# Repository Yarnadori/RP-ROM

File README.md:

# RP-ROM

M27C256 EPROM エミュレータ。RP2354A (RP2350 QFN-60) を搭載した自作 PCB で、32KB の ROM コンテンツを USB 経由で書き込み・読み出しできる。

## 概要

| 項目             | 内容                                            |
| ---------------- | ----------------------------------------------- |
| 対象 EPROM       | M27C256 互換 (32KB, 15-bit address, 8-bit data) |
| MCU              | RP2354A (RP2350 QFN-60, 360 MHz 動作)           |
| インターフェース | USB-C (CDC Serial)                              |
| フラッシュ保持   | 電源断後も ROM データを内蔵フラッシュに保存     |

## リポジトリ構成

```text
RP-ROM/
├── hardware/          # KiCad プロジェクト (回路図・PCB)
│   └── production/    # 製造用ファイル (BOM, Gerber, 部品配置)
├── software/          # RP2350 ファームウェア (C / Pico SDK)
│   └── main.c
└── tools/             # ホスト側 Python ツール
    └── rom_tool.py
```

## ハードウェア

KiCad で設計。製造 BOM の概要:

| Ref                 | 数量 | 部品 / 値                   | パッケージ / 備考              | LCSC Part # |
| ------------------- | ---: | --------------------------- | ------------------------------ | ----------- |
| IC1                 |    1 | RP2354A                     | QFN-60, メイン MCU             | C41378174   |
| U1                  |    1 | RT9080-33GJ5                | TSOT-23-5, 3.3V LDO            | C7528830    |
| J1                  |    1 | USB_C_Receptacle_USB2.0_16P | USB-C                          | C2843970    |
| J2, J3              |    2 | Conn_01x14_Pin              | 1×14 ピンヘッダ                |             |
| J4                  |    1 | Conn_01x03                  | JST SH 3P, デバッガー          | C7430452    |
| SW1                 |    1 | SW_Push                     | TS-1088 系タクトスイッチ       | C720477     |
| Y1                  |    1 | 12 MHz                      | 3225 4-pin 水晶                | C9002       |
| L1                  |    1 | 3.3uH                       | AOTA-B201610S3R3-101-T         | C42411119   |
| D1, D2              |    2 | RB521S-30                   | SOD-523 ショットキーダイオード | C8523       |
| D3                  |    1 | LED                         | 0402                           | C51933305   |
| C1                  |    1 | 4.7nF                       | 0402                           | C1538       |
| C2, C3              |    2 | 1uF                         | 0402                           | C52923      |
| C5, C8              |    2 | 15pF                        | 0402                           | C1548       |
| C9, C10, C11        |    3 | 4.7uF                       | 0402                           | C23733      |
| C4, C6, C7, C12-C14 |    6 | 0.1uF                       | 0402                           | C1525       |
| R1                  |    1 | 1MΩ                         | 0402                           | C26083      |
| R2, R3              |    2 | 5.1kΩ                       | 0402                           | C25905      |
| R4, R5, R6          |    3 | 1k                          | 0402                           | C11702      |
| R7, R8              |    2 | 27Ω                         | 0402                           | C25100      |
| R9                  |    1 | 33Ω                         | 0402                           | C25105      |

製造ファイルは `hardware/production/` に格納。

## ファームウェア

### 必要環境

- [Raspberry Pi Pico SDK](https://github.com/raspberrypi/pico-sdk) v2.2.0

### 動作

- **Core 1**: ROM アドレス線監視・データ出力 (フラッシュ不使用のタイトループ、360 MHz)
- **Core 0**: USB シリアル経由のコマンド処理
- **永続化**: 書き込んだ ROM データを内蔵フラッシュ末尾 36KB に保存。電源投入時に自動ロード。

## ツール (tools/)

Python 製のホストツール。詳細は [tools/README.md](tools/README.md) を参照。

```bash
cd tools
uv run rom_tool.py write COM3 firmware.hex
uv run rom_tool.py read  COM3 dump.bin
uv run rom_tool.py verify COM3 firmware.hex
uv run rom_tool.py erase COM3
uv run rom_tool.py info  COM3
```

対応フォーマット: `.bin` / Intel HEX (`.hex`)

## ライセンス

[MIT License](LICENSE)

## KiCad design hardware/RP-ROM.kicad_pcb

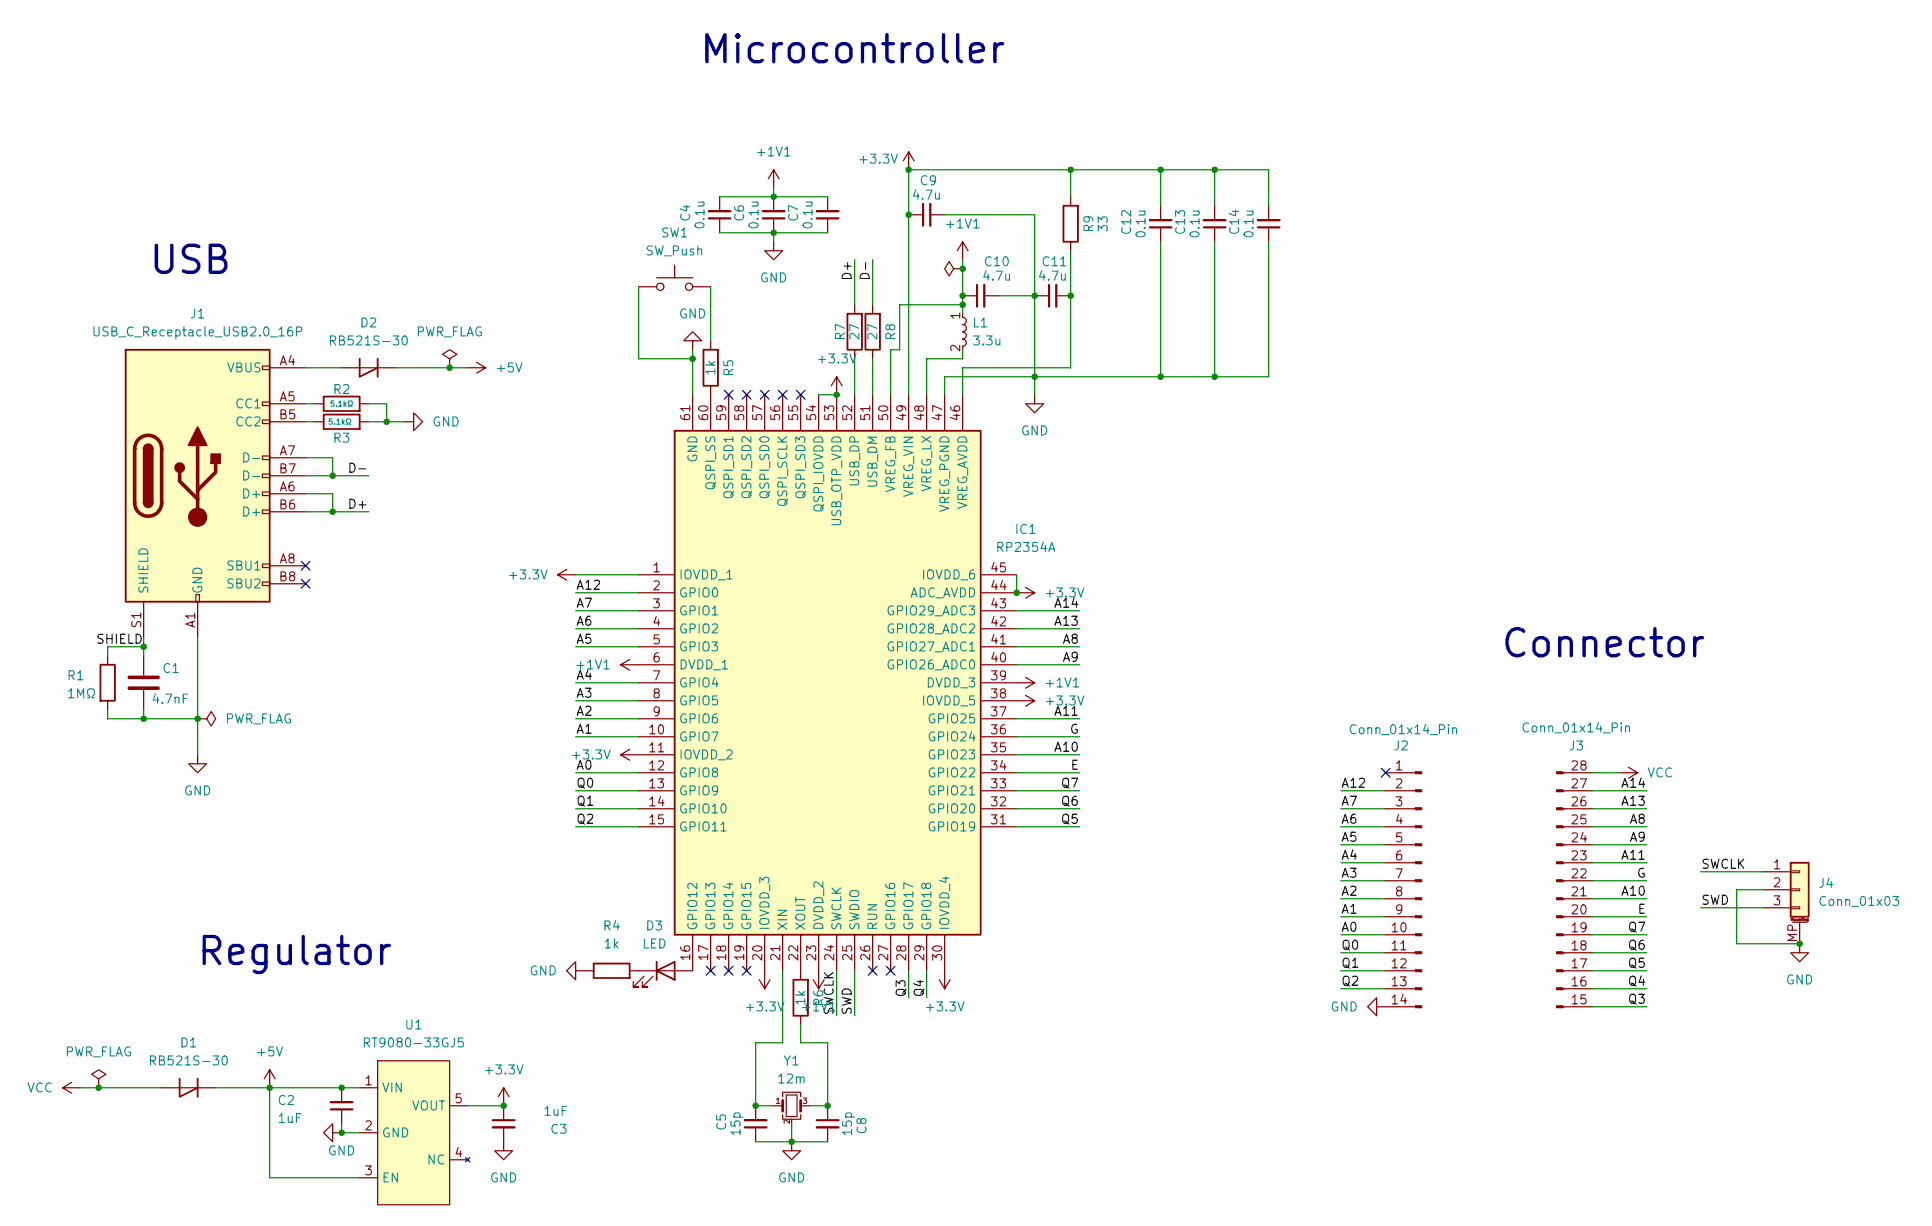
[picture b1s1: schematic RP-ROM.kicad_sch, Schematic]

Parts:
C1: 4.7nF; C_0402_1005Metric; JLCPCB Part # C1538
C2, C3: 1uF; C_0402_1005Metric; JLCPCB Part # C52923
C4, C6, C7, C12, C13, C14: 0.1u; C_0402_1005Metric; JLCPCB Part # C1525
C5, C8: 15p; C_0402_1005Metric; JLCPCB Part # C1548
C9, C10, C11: 4.7u; C_0402_1005Metric; JLCPCB Part # C23733
D1, D2: RB521S-30; D_SOD-523; JLCPCB Part # C8523
D3: LED; LED_0402_1005Metric; JLCPCB Part # C51933305
IC1: RP2354A; QFN-60-1EP_7x7mm_P0.4mm_EP3.4x3.4mm_ThermalVias; Manufacturer_Part_Number RP2354A; JLCPCB Part # C41378174
J1: USB_C_Receptacle_USB2.0_16P; USB_C_Receptacle_G-Switch_GT-USB-7051x; JLCPCB Part # C2843970
J2, J3: Conn_01x14_Pin; PinHeader_1x14_P2.54mm_Vertical
J4: Conn_01x03; JST_SH_BM03B-SRSS-TB_1x03-1MP_P1.00mm_Vertical; JLCPCB Part # C7430452
L1: 3.3u; AOTA-B201610S3R3-101-T; JLCPCB Part # C42411119
R1: 1MΩ; R_0402_1005Metric; JLCPCB Part # C26083
R2, R3: 5.1kΩ; R_0402_1005Metric; JLCPCB Part # C25905
R4, R5, R6: 1k; R_0402_1005Metric; JLCPCB Part # C11702
R7, R8: 27; R_0402_1005Metric; JLCPCB Part # C25100
R9: 33; R_0402_1005Metric; JLCPCB Part # C25105
SW1: SW_Push; SW_SPST_TS-1088-xR020; JLCPCB Part # C720477
U1: RT9080-33GJ5; TSOT-23-5; JLCPCB Part # C7528830
Y1: 12m; Crystal_SMD_3225-4Pin_3.2x2.5mm; JLCPCB Part # C9002

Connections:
+1V1: C4.2, C6.2, C7.2, C10.1, IC1.6 (DVDD_1), IC1.23 (DVDD_2), IC1.39 (DVDD_3), IC1.50 (VREG_FB), L1.1
+3.3V: C3.1, C9.1, C12.2, C13.2, C14.2, IC1.1 (IOVDD_1), IC1.11 (IOVDD_2), IC1.20 (IOVDD_3), IC1.30 (IOVDD_4), IC1.38 (IOVDD_5), IC1.44 (ADC_AVDD), IC1.45 (IOVDD_6), IC1.49 (VREG_VIN), IC1.53 (USB_OTP_VDD), IC1.54 (QSPI_IOVDD), R9.2, U1.5 (VOUT)
+5V: C2.2, D1.1 (K), D2.1 (K), U1.1 (VIN), U1.3 (EN)
/A0: IC1.12 (GPIO8), J2.10
/A1: IC1.10 (GPIO7), J2.9
/A2: IC1.9 (GPIO6), J2.8
/A3: IC1.8 (GPIO5), J2.7
/A4: IC1.7 (GPIO4), J2.6
/A5: IC1.5 (GPIO3), J2.5
/A6: IC1.4 (GPIO2), J2.4
/A7: IC1.3 (GPIO1), J2.3
/A8: IC1.41 (GPIO27_ADC1), J3.25 (Pin_11)
/A9: IC1.40 (GPIO26_ADC0), J3.24 (Pin_10)
/A10: IC1.35 (GPIO23), J3.21 (Pin_7)
/A11: IC1.37 (GPIO25), J3.23 (Pin_9)
/A12: IC1.2 (GPIO0), J2.2
/A13: IC1.42 (GPIO28_ADC2), J3.26 (Pin_12)
/A14: IC1.43 (GPIO29_ADC3), J3.27 (Pin_13)
/D+: J1.A6 (D+), J1.B6 (D+), R7.2
/D-: J1.A7 (D-), J1.B7 (D-), R8.2
/E: IC1.34 (GPIO22), J3.20 (Pin_6)
/G: IC1.36 (GPIO24), J3.22 (Pin_8)
/Q0: IC1.13 (GPIO9), J2.11
/Q1: IC1.14 (GPIO10), J2.12
/Q2: IC1.15 (GPIO11), J2.13
/Q3: IC1.28 (GPIO17), J3.15 (Pin_1)
/Q4: IC1.29 (GPIO18), J3.16 (Pin_2)
/Q5: IC1.31 (GPIO19), J3.17 (Pin_3)
/Q6: IC1.32 (GPIO20), J3.18 (Pin_4)
/Q7: IC1.33 (GPIO21), J3.19 (Pin_5)
/SHIELD: C1.1, J1.S1 (SHIELD), R1.1
/SWCLK: IC1.24 (SWCLK), J4.1
/SWD: IC1.25 (SWDIO), J4.3
GND: C1.2, C2.1, C3.2, C4.1, C5.1, C6.1, C7.1, C8.2, C9.2, C10.2, C11.1, C12.1, C13.1, C14.1, IC1.47 (VREG_PGND), IC1.61 (GND), J1.A1 (GND), J1.A12 (GND), J1.B1 (GND), J1.B12 (GND), J2.14, J4.2, J4.MP (MountPin), R1.2, R2.2, R3.2, R4.1, SW1.1, U1.2 (GND), Y1.2 (G), Y1.4 (G)
unnamed: C8.1, R6.1, Y1.3
unnamed: D2.2 (A), J1.A4 (VBUS), J1.A9 (VBUS), J1.B4 (VBUS), J1.B9 (VBUS)
unnamed: D3.2 (A), IC1.16 (GPIO12)
unnamed: D3.1 (K), R4.2
unnamed: IC1.60 (QSPI_SS), R5.1
unnamed: IC1.51 (USB_DM), R8.1
unnamed: IC1.52 (USB_DP), R7.1
unnamed: C11.2, IC1.46 (VREG_AVDD), R9.1
unnamed: IC1.48 (VREG_LX), L1.2
unnamed: C5.2, IC1.21 (XIN), Y1.1
unnamed: IC1.22 (XOUT), R6.2
unnamed: J1.A5 (CC1), R2.1
unnamed: J1.B5 (CC2), R3.1
unnamed: R5.2, SW1.2
VCC: D1.2 (A), J3.28 (Pin_14)

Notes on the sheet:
Connector
Regulator
Microcontroller
USB

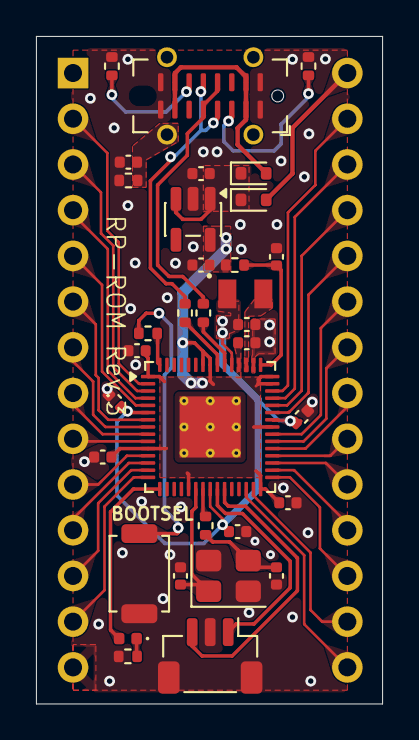
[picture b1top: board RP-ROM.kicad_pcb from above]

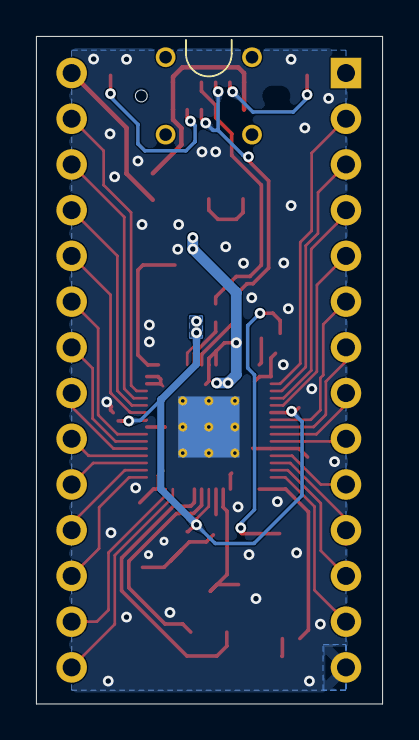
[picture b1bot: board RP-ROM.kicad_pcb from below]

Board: 2 copper layers, 19.2 x 37.1 mm, 35 parts (2 on the bottom side), 49 nets.

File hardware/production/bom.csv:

Designator,Footprint,Quantity,Value,LCSC Part #
C1,0402,1,4.7nF,C1538
"C10, C11, C9",0402,3,4.7u,C23733
"C12, C13, C14, C4, C6, C7",0402,6,0.1u,C1525
"C2, C3",0402,2,1uF,C52923
"C5, C8",0402,2,15p,C1548
"D1, D2",D_SOD-523,2,RB521S-30,C8523
D3,0402,1,LED,C51933305
IC1,QFN-60-1EP_7x7mm_P0.4mm_EP3.4x3.4mm_ThermalVias,1,RP2354A,C41378174
J1,USB_C_Receptacle_G-Switch_GT-USB-7051x,1,USB_C_Receptacle_USB2.0_16P,C2843970
"J2, J3",PinHeader_1x14_P2.54mm_Vertical,2,Conn_01x14_Pin,
J4,JST_SH_BM03B-SRSS-TB_1x03-1MP_P1.00mm_Vertical,1,Conn_01x03,C7430452
L1,AOTA-B201610S3R3-101-T,1,3.3u,C42411119
R1,0402,1,1MΩ,C26083
"R2, R3",0402,2,5.1kΩ,C25905
"R4, R5, R6",0402,3,1k,C11702
"R7, R8",0402,2,27,C25100
R9,0402,1,33,C25105
SW1,SW_SPST_TS-1088-xR020,1,SW_Push,C720477
U1,TSOT-23-5,1,RT9080-33GJ5,C7528830
Y1,Crystal_SMD_3225-4Pin_3.2x2.5mm,1,12m,C9002

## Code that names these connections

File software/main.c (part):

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static volatile bool core1_paused = false;

// gpio_lo_lut[i]: i = GPIO[8:0] (9-bit), result = partial address from A0,A1-A7,A12
//   GPIO0=A12, GPIO1=A7, GPIO2=A6, GPIO3=A5, GPIO4=A4, GPIO5=A3, GPIO6=A2, GPIO7=A1, GPIO8=A0
// GPIO8(A0) is folded in to eliminate the separate | ((g>>8)&1) op in the hot loop
static uint16_t gpio_lo_lut[512];

// gpio_hi_lut[i]: i = GPIO[29:23] packed into 7 bits, result = partial address from A8-A14
//   bit0(GPIO23)=A10, bit1(GPIO24)=CE#(skip), bit2(GPIO25)=A11,
//   bit3(GPIO26)=A9,  bit4(GPIO27)=A8, bit5(GPIO28)=A13, bit6(GPIO29)=A14
static uint16_t gpio_hi_lut[128];

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    for (int i = 0; i < 512; i++)
    {
        uint16_t a = 0;
        a |= (uint16_t)(((i >> 0) & 1) << 12); // GPIO0 -> A12
        a |= (uint16_t)(((i >> 1) & 1) << 7);  // GPIO1 -> A7
        a |= (uint16_t)(((i >> 2) & 1) << 6);  // GPIO2 -> A6
        a |= (uint16_t)(((i >> 3) & 1) << 5);  // GPIO3 -> A5
        a |= (uint16_t)(((i >> 4) & 1) << 4);  // GPIO4 -> A4
        a |= (uint16_t)(((i >> 5) & 1) << 3);  // GPIO5 -> A3
        a |= (uint16_t)(((i >> 6) & 1) << 2);  // GPIO6 -> A2
        a |= (uint16_t)(((i >> 7) & 1) << 1);  // GPIO7 -> A1
        a |= (uint16_t)(((i >> 8) & 1) << 0);  // GPIO8 -> A0
        gpio_lo_lut[i] = a;
    }
    for (int i = 0; i < 128; i++)
    {
        uint16_t a = 0;
        a |= (uint16_t)(((i >> 0) & 1) << 10); // bit0 (GPIO23) -> A10
        // bit1 (GPIO24) = CE#, skip
        a |= (uint16_t)(((i >> 2) & 1) << 11); // bit2 (GPIO25) -> A11
        a |= (uint16_t)(((i >> 3) & 1) << 9);  // bit3 (GPIO26) -> A9
        a |= (uint16_t)(((i >> 4) & 1) << 8);  // bit4 (GPIO27) -> A8
        a |= (uint16_t)(((i >> 5) & 1) << 13); // bit5 (GPIO28) -> A13
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
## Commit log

2026-04-26 Init
2026-04-26 READMEの修正
2026-05-08 Rev2
2026-05-11 Rev3
